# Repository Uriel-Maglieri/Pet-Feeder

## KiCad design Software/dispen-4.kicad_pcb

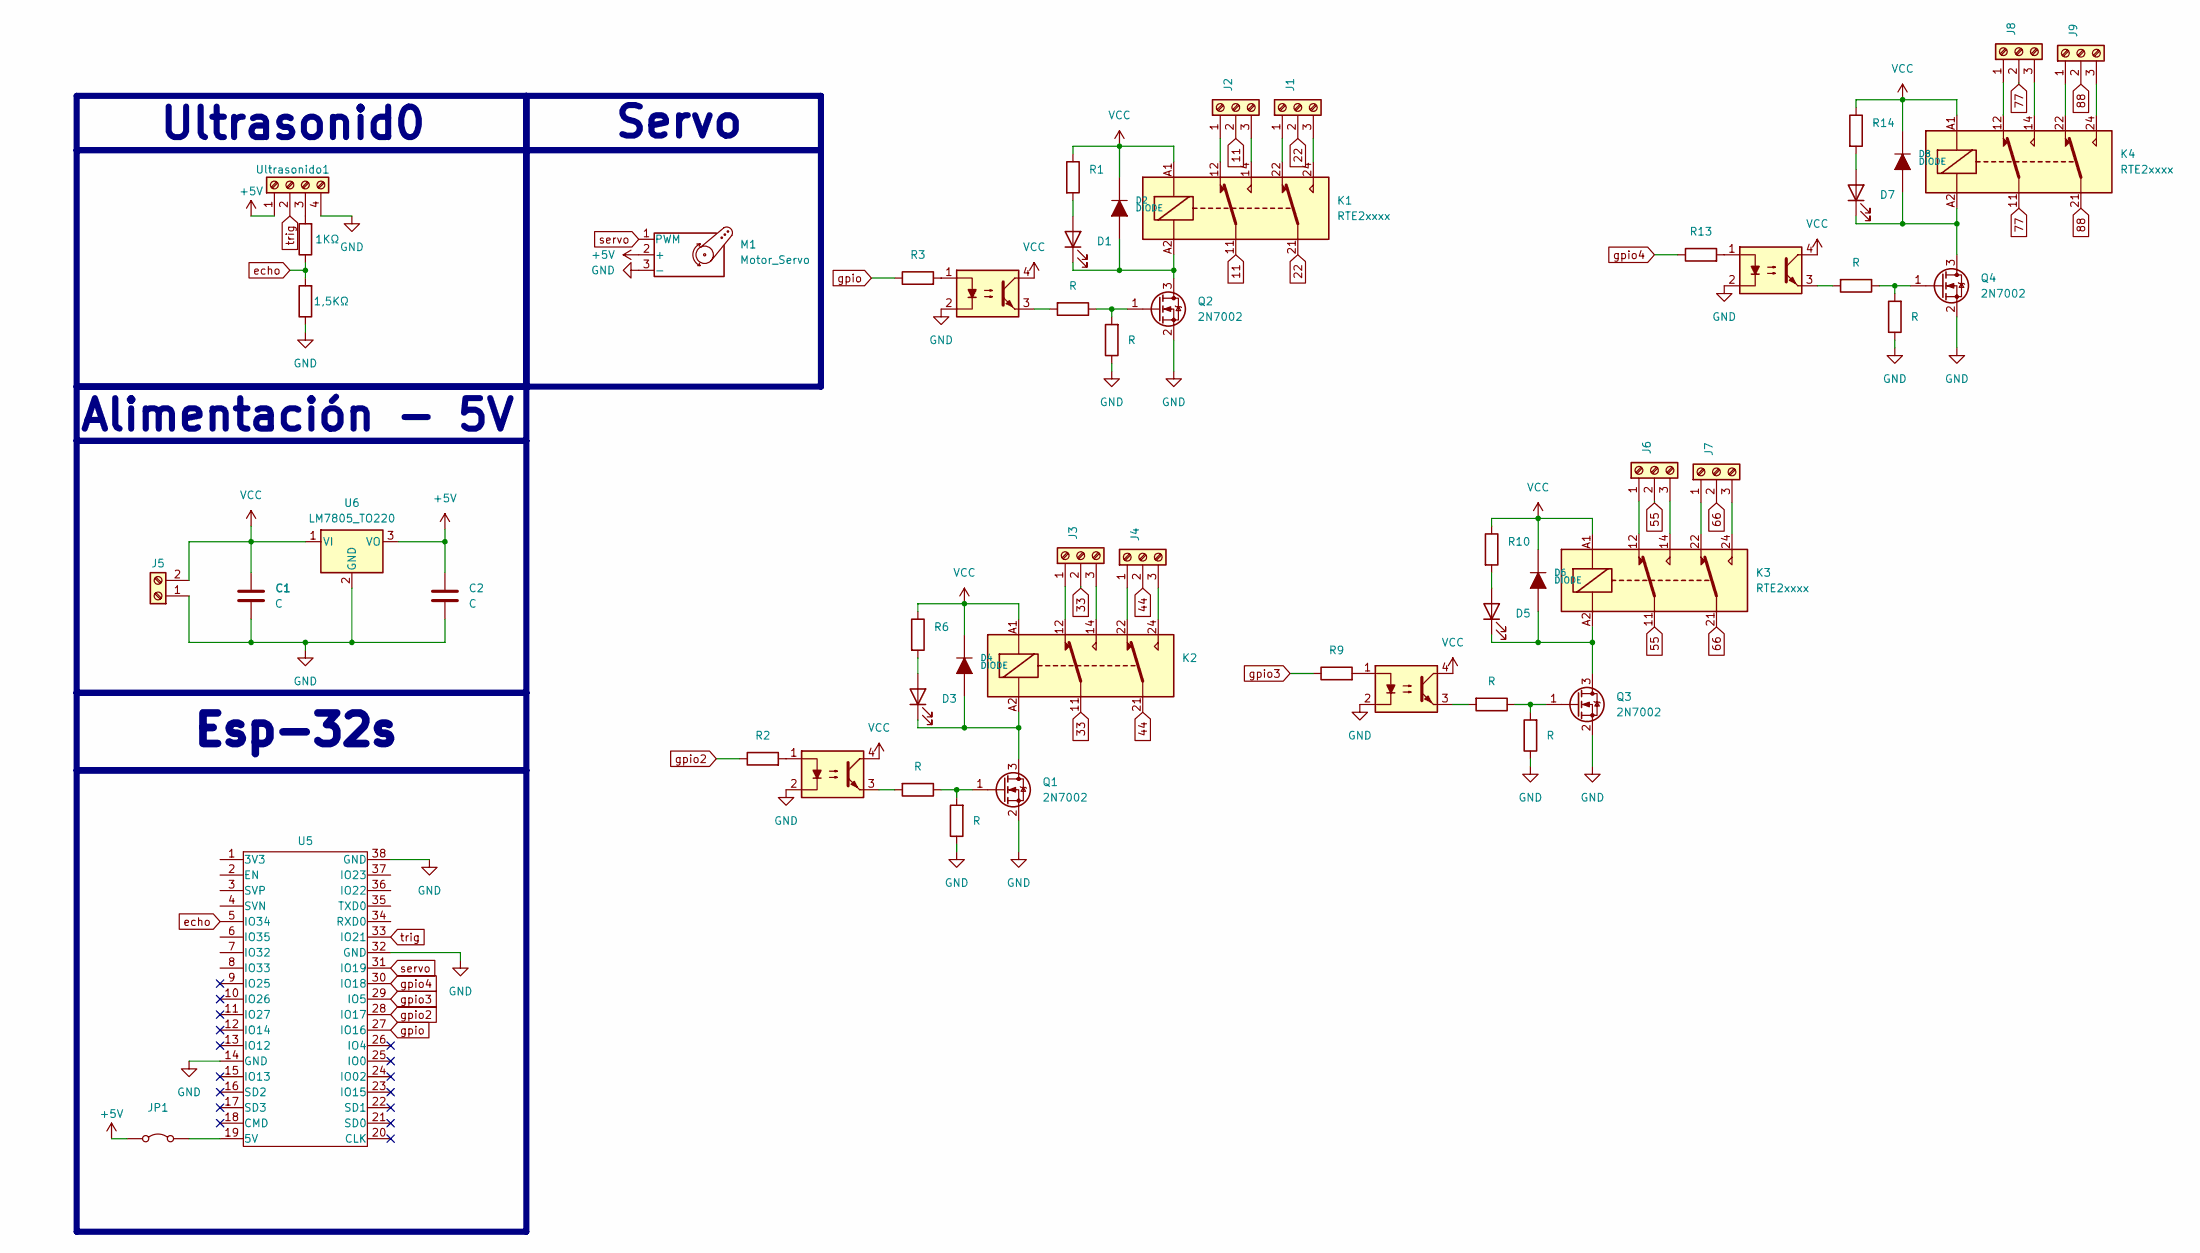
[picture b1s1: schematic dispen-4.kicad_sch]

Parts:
C1, C2: C; C_0805_2012Metric
D1, D3, D5, D7: LED; LED_0805_2012Metric
D2, D4, D6, D8: DIODE; D_0805_2012Metric
J1, J2, J3, J4, J6, J7, J8, J9: Screw_Terminal_01x03; TerminalBlock_Xinya_XY308-2.54-3P_1x03_P2.54mm_Horizontal
J5: Screw_Terminal_01x02; TerminalBlock_Xinya_XY308-2.54-2P_1x02_P2.54mm_Horizontal
JP1: Jumper_2_Bridged; PinHeader_1x02_P2.54mm_Vertical
K1, K2, K3, K4: RTE2xxxx; Relay_DPDT_Schrack-RT2-FormC_RM5mm
M1: Motor_Servo; JST_XA_B03B-XASK-1-A_1x03_P2.50mm_Vertical
Q1, Q2, Q3, Q4: 2N7002; SOT-23
R1, R2, R3, R4, R5, R6, R7, R8, R9, R10, R11, R12, R13, R14, R15, R16: R; R_0805_2012Metric
R17: 1KΩ; R_0805_2012Metric
R18: 1,5KΩ; R_0805_2012Metric
U1, U2, U3, U4: PC817; DIP762W50P254L650H455Q4B
U5: ESP32_DEVKITC; ESP32S
U6: LM7805_TO220; TO-220-3_Vertical
Ultrasonido1: Screw_Terminal_01x04; TerminalBlock_Xinya_XY308-2.54-4P_1x04_P2.54mm_Horizontal

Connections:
11: J2.2, K1.11
22: J1.2, K1.21
33: J3.2, K2.11
44: J4.2, K2.21
55: J6.2, K3.11
66: J7.2, K3.21
77: J8.2, K4.11
88: J9.2, K4.21
+5V: C2.1, JP1.1 (A), M1.2 (+), U6.3 (VO), Ultrasonido1.1
GND: C1.2, C2.2, J5.1, M1.3 (-), Q1.2 (S), Q2.2 (S), Q3.2 (S), Q4.2 (S), R4.1, R8.1, R12.1, R16.1, R18.1, U1.2, U2.2, U3.2, U4.2, U5.14 (GND), U5.32 (GND), U5.38 (GND), U6.2 (GND), Ultrasonido1.4
unnamed: D1.2 (A), R1.2
unnamed: D1.1 (K), D2.1 (A), K1.A2, Q2.3 (D)
unnamed: D3.2 (A), R6.2
unnamed: D3.1 (K), D4.1 (A), K2.A2, Q1.3 (D)
unnamed: D5.2 (A), R10.2
unnamed: D5.1 (K), D6.1 (A), K3.A2, Q3.3 (D)
unnamed: D7.2 (A), R14.2
unnamed: D7.1 (K), D8.1 (A), K4.A2, Q4.3 (D)
unnamed: J1.1, K1.22
unnamed: J1.3, K1.24
unnamed: J2.1, K1.12
unnamed: J2.3, K1.14
unnamed: J3.1, K2.12
unnamed: J3.3, K2.14
unnamed: J4.1, K2.22
unnamed: J4.3, K2.24
unnamed: J6.1, K3.12
unnamed: J6.3, K3.14
unnamed: J7.1, K3.22
unnamed: J7.3, K3.24
unnamed: J8.1, K4.12
unnamed: J8.3, K4.14
unnamed: J9.1, K4.22
unnamed: J9.3, K4.24
unnamed: JP1.2 (B), U5.19 (5V)
unnamed: Q1.1 (G), R7.1, R8.2
unnamed: Q2.1 (G), R4.2, R5.1
unnamed: Q3.1 (G), R11.1, R12.2
unnamed: Q4.1 (G), R15.1, R16.2
unnamed: R2.2, U2.1
unnamed: R3.2, U1.1
unnamed: R5.2, U1.3
unnamed: R7.2, U2.3
unnamed: R9.2, U3.1
unnamed: R11.2, U3.3
unnamed: R13.2, U4.1
unnamed: R15.2, U4.3
unnamed: R17.2, Ultrasonido1.3
VCC: C1.1, D2.2 (K), D4.2 (K), D6.2 (K), D8.2 (K), J5.2, K1.A1, K2.A1, K3.A1, K4.A1, R1.1, R6.1, R10.1, R14.1, U1.4, U2.4, U3.4, U4.4, U6.1 (VI)
echo: R17.1, R18.2, U5.5 (IO34)
gpio: R3.1, U5.27 (IO16)
gpio2: R2.1, U5.28 (IO17)
gpio3: R9.1, U5.29 (IO5)
gpio4: R13.1, U5.30 (IO18)
servo: M1.1 (PWM), U5.31 (IO19)
trig: U5.33 (IO21), Ultrasonido1.2

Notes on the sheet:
Esp-32s
Alimentación - 5V
Ultrasonid0
Servo

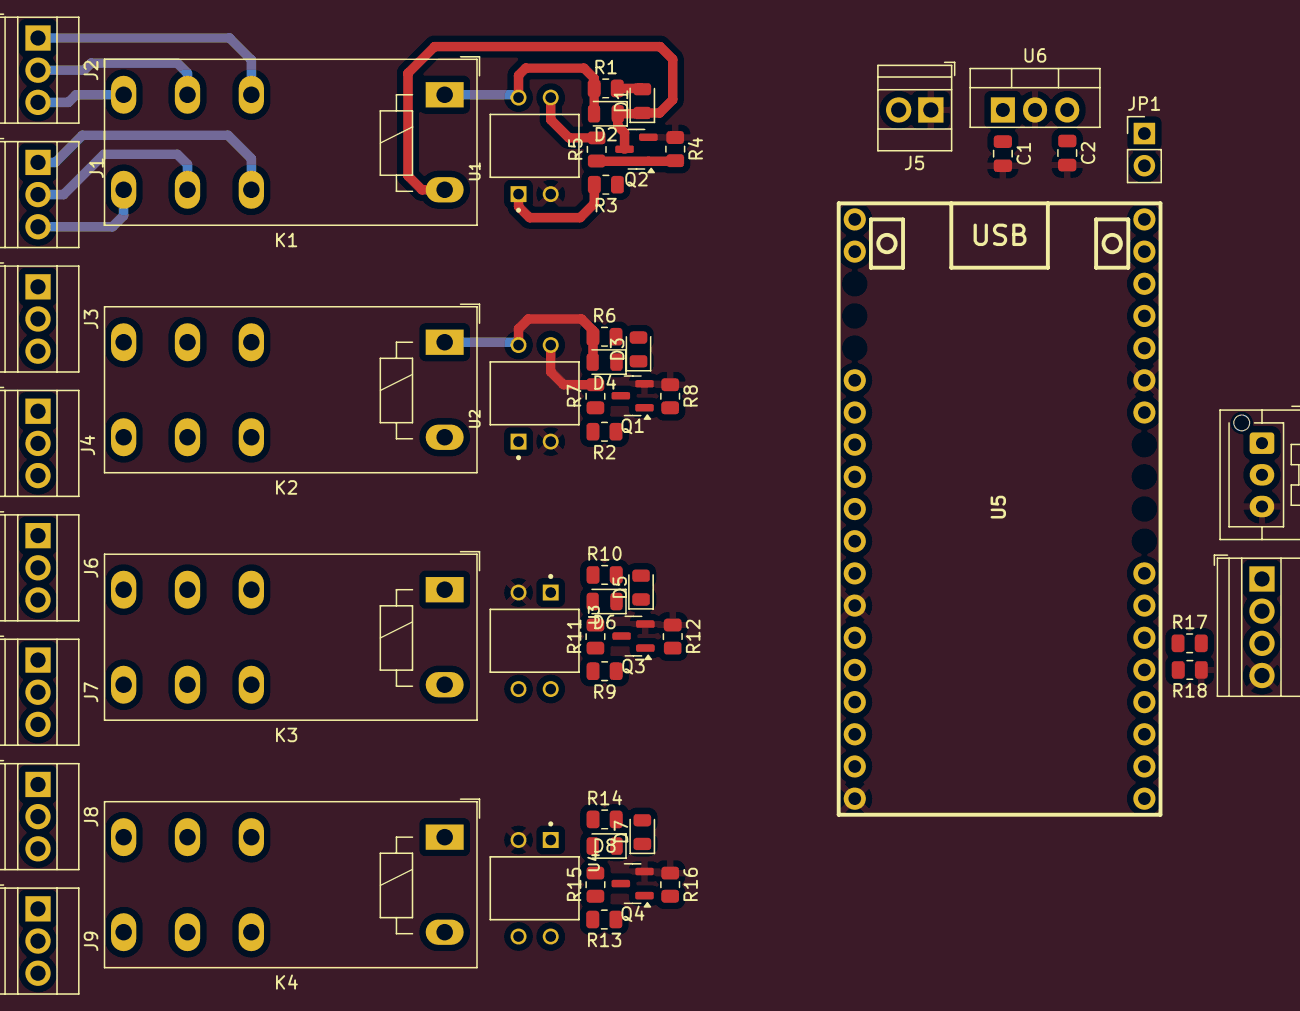
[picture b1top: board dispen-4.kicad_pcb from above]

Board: 2 copper layers, 54 parts (0 on the bottom side), 56 nets.

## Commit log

2025-05-13 Primer Commit
2025-05-14 Segundo commit
